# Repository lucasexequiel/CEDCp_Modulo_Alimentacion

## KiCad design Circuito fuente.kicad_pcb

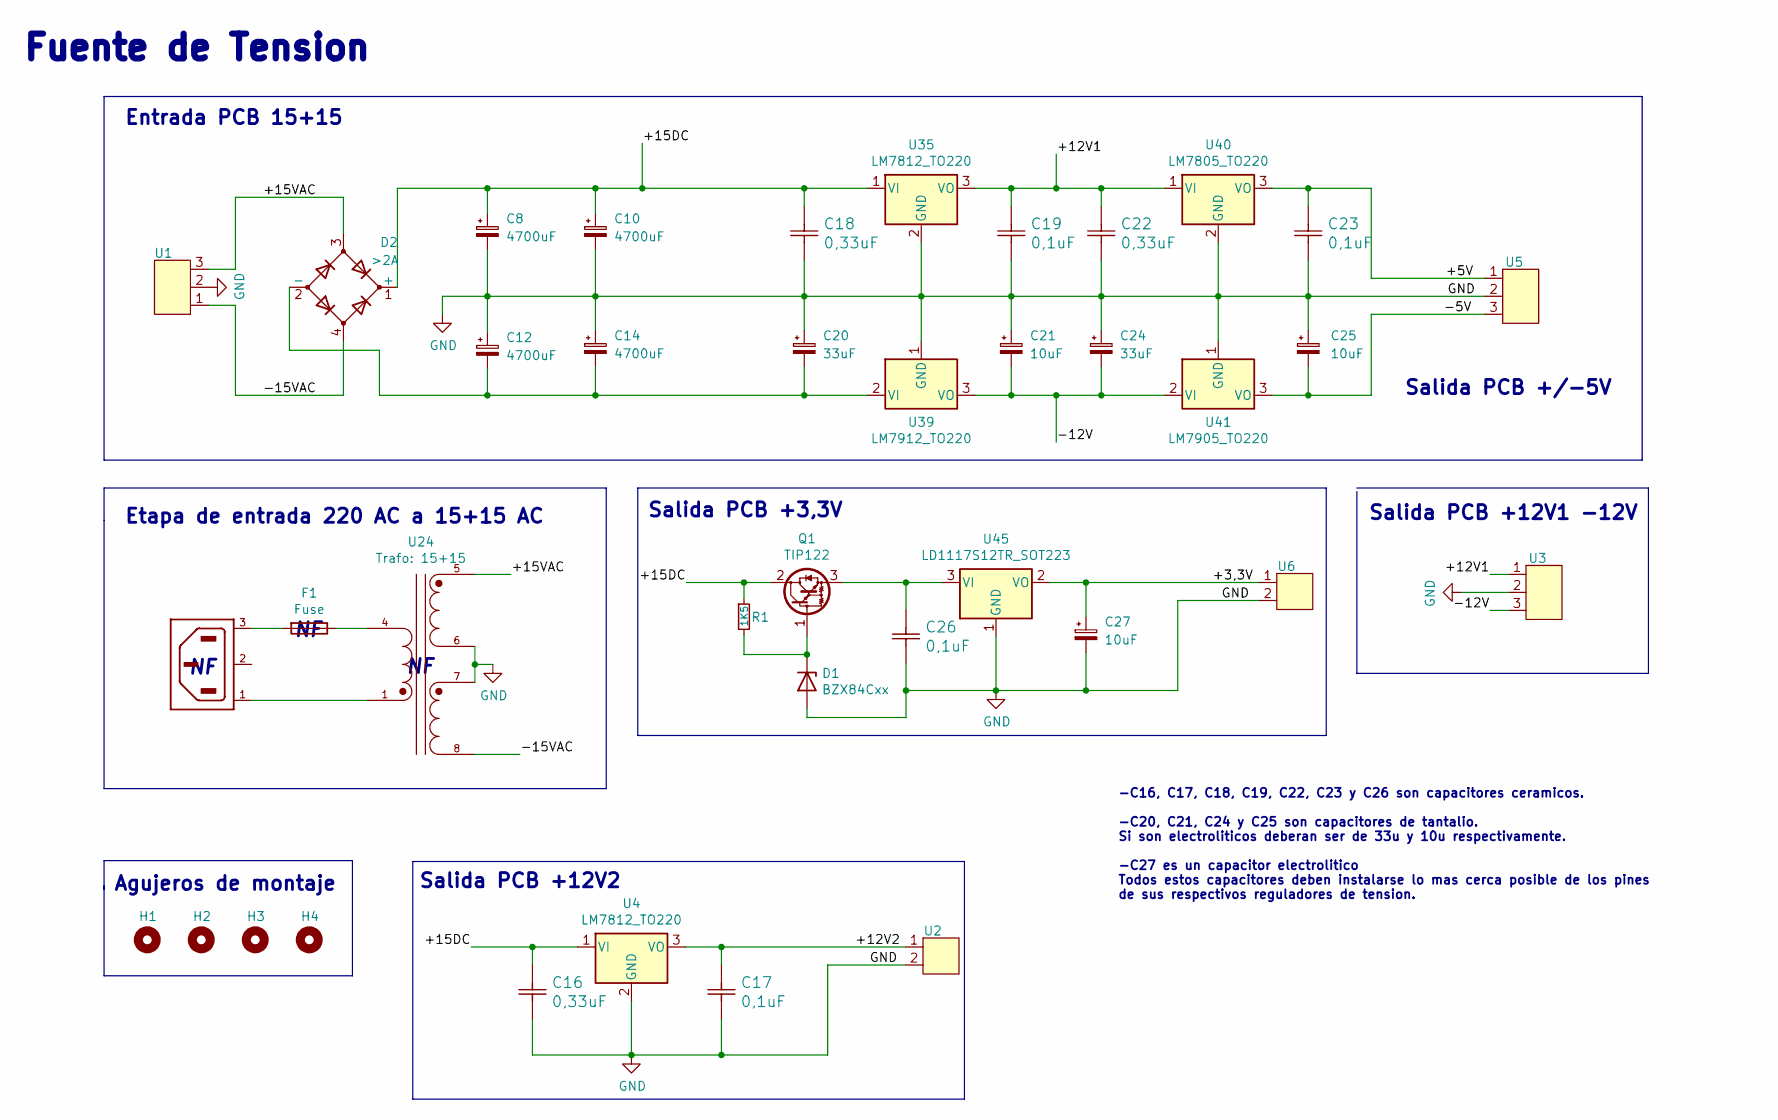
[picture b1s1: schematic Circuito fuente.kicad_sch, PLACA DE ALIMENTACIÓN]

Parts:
C8, C12: 4700uF; Cap_4700uF_50V
C10, C14: 4700uF; Cap_4700uF_35V
C16, C18, C22: 0,33uF; C_Disc_D7.5mm_W2.5mm_P5.00mm
C17, C19, C23, C26: 0,1uF; C_Disc_D7.5mm_W2.5mm_P5.00mm
C20, C24: 33uF; Cap_1uF
C21, C25, C27: 10uF; Cap_1uF
D1: BZX84Cxx; D_A-405_P7.62mm_Horizontal
D2: >2A; Diode_Bridge_15.2x15.2x6.3mm_P10.9mm
F1: Fuse
H1, H2, H3, H4: MountingHole; MountingHole_3.2mm_M3_Pad_Via
Q1: TIP122; TO-220-3_Vertical
R1: 1K5; Resistencia_0,25W
U1, U3, U5: Bornera_1x3
U2, U6: Bornera_1x2
U4, U35: LM7812_TO220; TO-220-3_Vertical
U24: Trafo: 15+15; PARTREV ST/DST Series 12.19
U39: LM7912_TO220; TO-220-3_Vertical
U40: LM7805_TO220; TO-220-3_Vertical
U41: LM7905_TO220; TO-220-3_Vertical
U45: LD1117S12TR_SOT223; TO-220-3_Vertical
X1: 6ESRM-P

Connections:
/+3,3V: C27.1, U6.1, U45.2 (VO)
/+5V: C23.1, U5.1, U40.3 (VO)
/+12V1: C19.1, C22.1, U3.1, U35.3 (VO), U40.1 (VI)
/+12V2: C17.1, U2.1, U4.3 (VO)
/+15DC: C8.1, C10.1, C16.1, C18.1, D2.1 (+), Q1.2 (C), R1.1, U4.1 (VI), U35.1 (VI)
/+15VAC: D2.3, U1.3, U24.5
/-5V: C25.2, U5.3, U41.3 (VO)
/-12V: C21.2, C24.2, U3.3, U39.3 (VO), U41.2 (VI)
/-15VAC: D2.4, U1.1, U24.8
GND: C8.2, C10.2, C12.1, C14.1, C16.2, C17.2, C18.2, C19.2, C20.1, C21.1, C22.2, C23.2, C24.1, C25.1, C26.2, C27.2, D1.2 (A), U1.2, U2.2, U3.2, U4.2 (GND), U5.2, U6.2, U24.6, U24.7, U35.2 (GND), U39.1 (GND), U40.2 (GND), U41.1 (GND), U45.1 (GND)
unnamed: C12.2, C14.2, C20.2, D2.2 (-), U39.2 (VI)
unnamed: C26.1, Q1.3 (E), U45.3 (VI)
unnamed: D1.1 (K), Q1.1 (B), R1.2
unnamed: F1.1, U24.4
unnamed: F1.2, X1.3
unnamed: U24.1, X1.1

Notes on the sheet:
Salida PCB +/-5V
Etapa de entrada 220 AC a 15+15 AC
Salida PCB +3,3V
Fuente de Tension
Salida PCB +12V1 -12V
Salida PCB +12V2
Entrada PCB 15+15
-C16, C17, C18, C19, C22, C23 y C26 son capacitores ceramicos. -C20, C21, C24 y C25 son capacitores de tantalio. Si son electroliticos deberan ser de 33u y 10u respectivamente. -C27 es un capacitor electrolitico Todos estos capacitores deben instalarse lo mas cerca posible de los pines de sus respe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
Agujeros de montaje

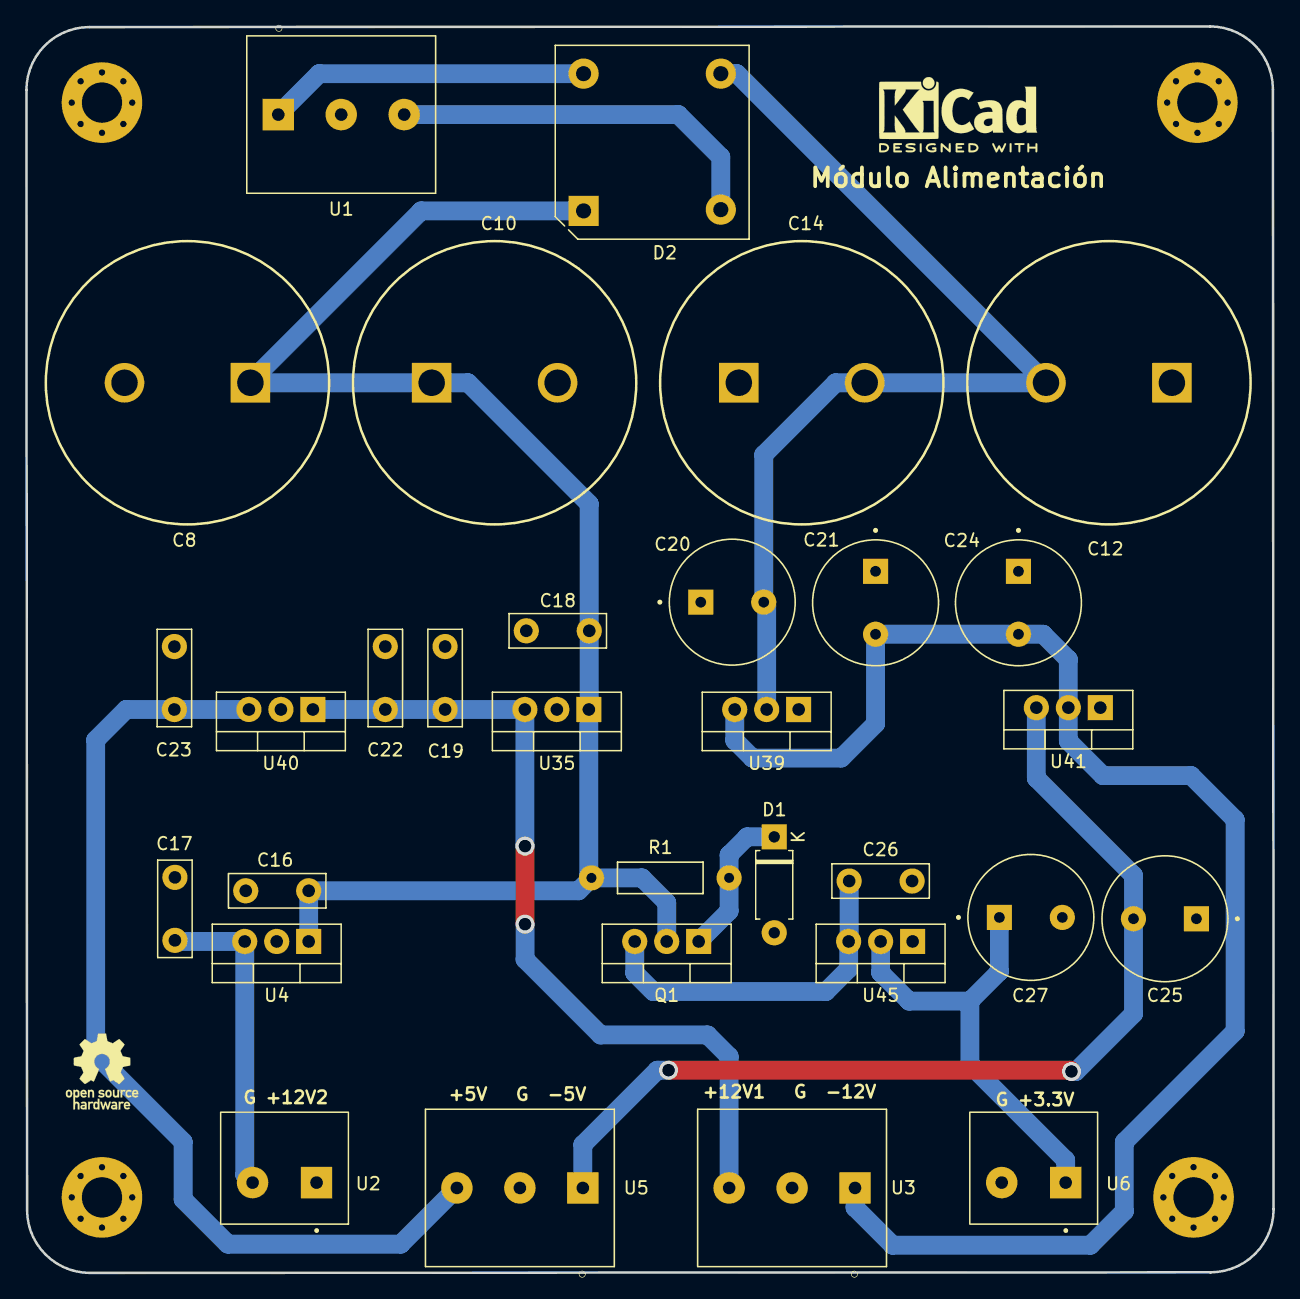
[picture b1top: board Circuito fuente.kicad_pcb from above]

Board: 2 copper layers, 99.1 x 99.0 mm, 35 parts (0 on the bottom side), 13 nets.

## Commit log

2022-02-05 Create README.md
    Add README file
2022-02-05 Added Kicad files Modulo de alimentacion project
2022-02-10 De 2 a 1 Layer + 3D model add
2022-02-12 Gerbers files generated
2022-02-18 Replacement name
2022-02-28 Reordering schematic
2022-02-28 Gerbers Modified
2022-03-06 Version V1 (Schematic + clearence)
2022-03-15 Printed supply board with pdf
2022-03-16 Heat sink added
2022-04-15 Last version

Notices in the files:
Circuito fuente.kicad_pcb:
creativecommons.orgn/licenses/by/4.0
License: CC BY 4.0
Circuito fuente.kicad_sch:
creativecommons.org/licenses/by/4.0
